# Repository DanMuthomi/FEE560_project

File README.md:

This is a repository for my BSc. Electrical Engineering final year project

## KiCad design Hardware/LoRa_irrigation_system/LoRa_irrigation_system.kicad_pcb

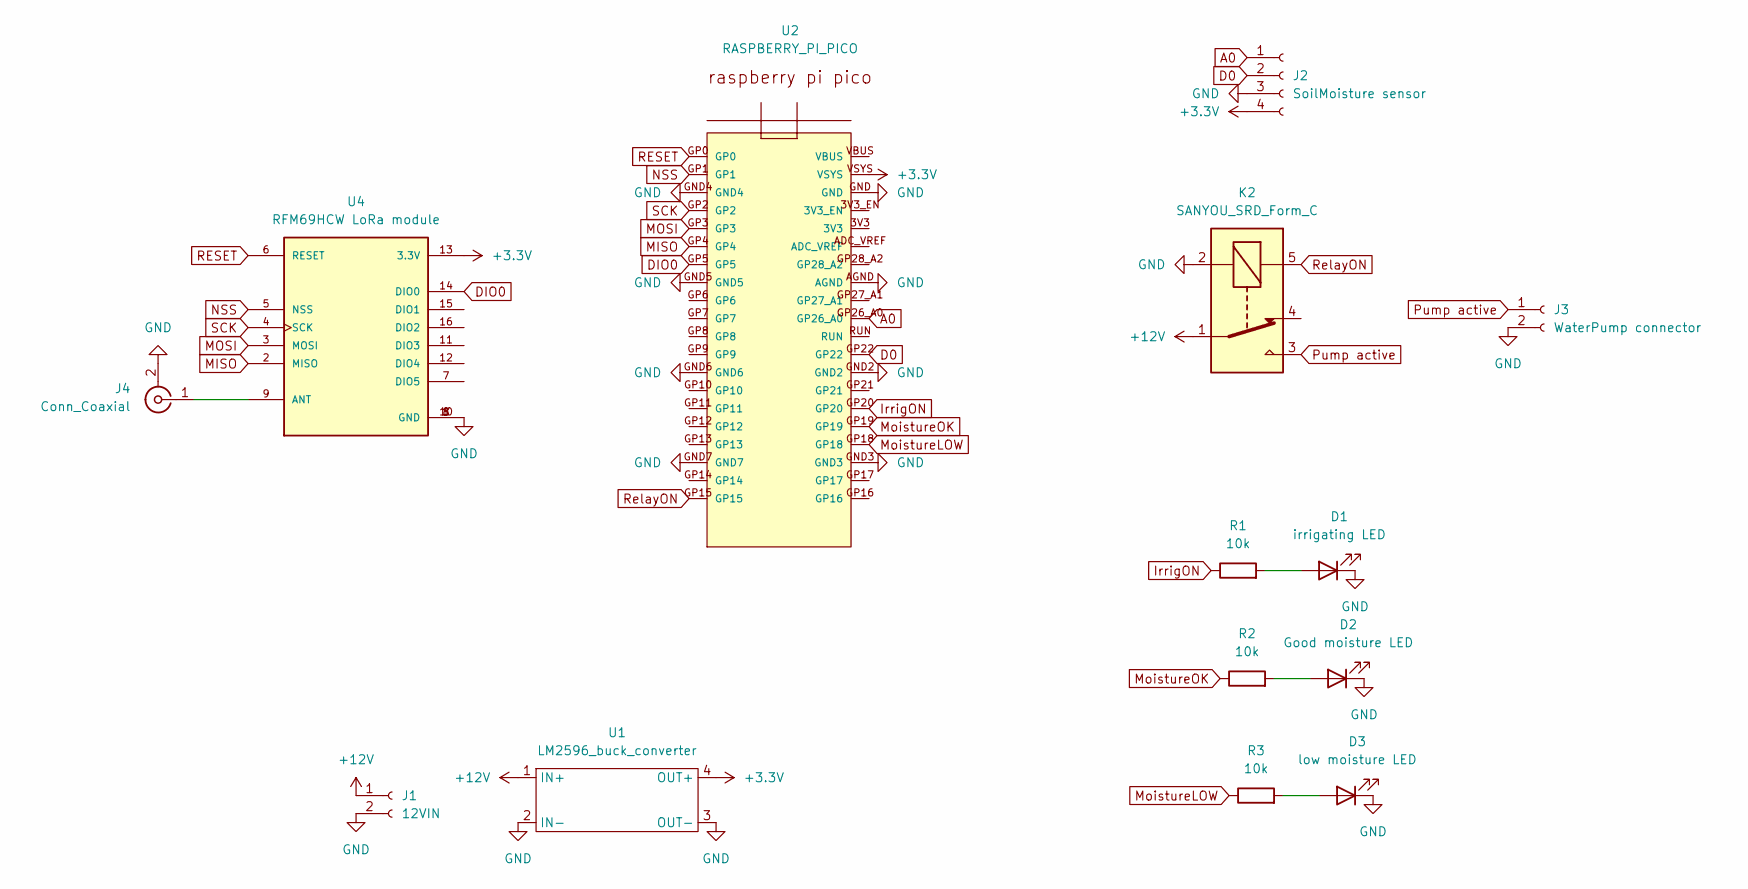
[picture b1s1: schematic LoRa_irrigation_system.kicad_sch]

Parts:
D1: irrigating LED; LED_D5.0mm_Clear
D2: Good moisture LED; LED_D5.0mm_Clear
D3: low moisture LED; LED_D5.0mm_Clear
J1: 12VIN; TerminalBlock_Phoenix_PT-1,5-2-5.0-H_1x02_P5.00mm_Horizontal
J2: SoilMoisture sensor; PinSocket_1x04_P2.54mm_Vertical
J3: WaterPump connector; TerminalBlock_Phoenix_PT-1,5-2-3.5-H_1x02_P3.50mm_Horizontal
J4: Conn_Coaxial; SMA_Amphenol_132134_Vertical
K2: SANYOU_SRD_Form_C; Relay_SPDT_SANYOU_SRD_Series_Form_C
R1, R2, R3: 10k; R_Axial_DIN0309_L9.0mm_D3.2mm_P12.70mm_Horizontal
U1: LM2596_buck_converter; LM2596_Buck converter
U2: RASPBERRY_PI_PICO
U4: RFM69HCW LoRa module

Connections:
+3.3V: J2.4, U1.4 (OUT+), U2.VSYS, U4.13 (3.3V)
+12V: J1.1, K2.1, U1.1 (IN+)
A0: J2.1, U2.GP26_A0
D0: J2.2, U2.GP22
DIO0: U2.GP5, U4.14 (DIO0)
GND: D1.1 (K), D2.1 (K), D3.1 (K), J1.2, J2.3, J3.2, J4.2 (Ext), K2.2, U1.2 (IN-), U1.3 (OUT-), U2.AGND, U2.GND, U2.GND2, U2.GND3, U2.GND4, U2.GND5, U2.GND6, U2.GND7, U4.1 (GND), U4.8 (GND), U4.10 (GND)
IrrigON: R1.1, U2.GP20
MISO: U2.GP4, U4.2 (MISO)
MOSI: U2.GP3, U4.3 (MOSI)
MoistureLOW: R3.1, U2.GP18
MoistureOK: R2.1, U2.GP19
NSS: U2.GP1, U4.5 (NSS)
unnamed: D1.2 (A), R1.2
unnamed: D2.2 (A), R2.2
unnamed: D3.2 (A), R3.2
unnamed: J4.1 (In), U4.9 (ANT)
Pump active: J3.1, K2.3
RESET: U2.GP0, U4.6 (RESET)
RelayON: K2.5, U2.GP15
SCK: U2.GP2, U4.4 (SCK)

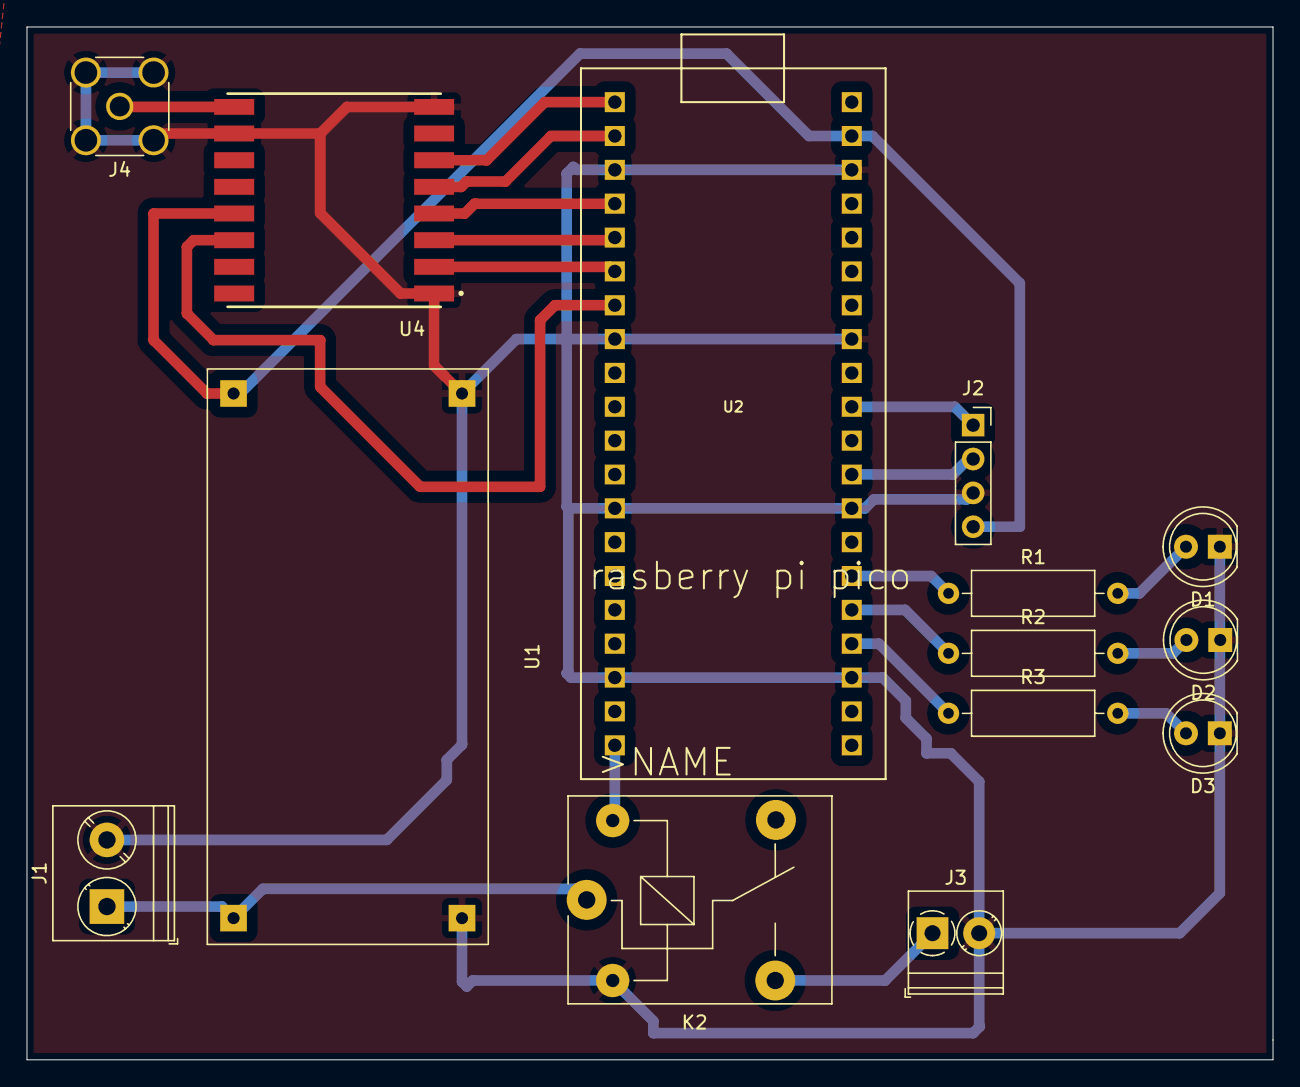
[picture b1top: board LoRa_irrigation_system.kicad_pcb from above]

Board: 2 copper layers, 93.5 x 77.5 mm, 14 parts (0 on the bottom side), 20 nets.

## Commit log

2024-04-17 adding readme
2024-04-17 PCB design start
2024-04-22 Sschematic design
2024-04-28 SCH complete*
2024-04-28 PCB design complete*
2024-04-29 backup
2024-04-29 SWare start
2024-04-29 links update
2024-05-07 backups
2024-05-10 updated sample codes
2024-05-10 testing out LoRa with ThingsNetwork
2024-05-11 Project screenshots
2024-05-11 design mods
2024-05-11 pump code screenshot
2024-05-16 working sender code from pico
2024-05-16 arduino lora code. receiver code working: receiving messages from pico
2024-05-16 updating interesting links
2024-05-20 combined code with all the functions
2024-05-20 soil_moisture sendor code
2024-05-20 updated moist_pump_lora code
2024-05-21 interesting links updated
2024-05-29 H/ware updates
2024-05-29 Different LoRa versions for testing
2024-05-30 Updated ulora_v2 with working devadd components. needs work to remove encryption
2024-06-21 Updated codes for string and json
2024-06-21 Updated design for V2 board
2024-06-24 full code with moisture sensing et-al
2024-06-24 sending consistent data to server
2024-06-24 Updated to save frame counters
2024-06-24 working well includingviewing data on server
2024-06-24 adding the key library link
2024-06-25 updated firmware with appropriate comments
2024-06-25 new report screenshots
2024-06-26 updated hardware
2024-06-26 Final code coopy
